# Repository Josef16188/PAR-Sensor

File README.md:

FloraFlux – PAR Sensor

FloraFlux is a custom-built sensor for measuring Photosynthetic Photon Flux Density (PPFD) and calculating the Daily Light Integral (DLI) for plant-light monitoring.

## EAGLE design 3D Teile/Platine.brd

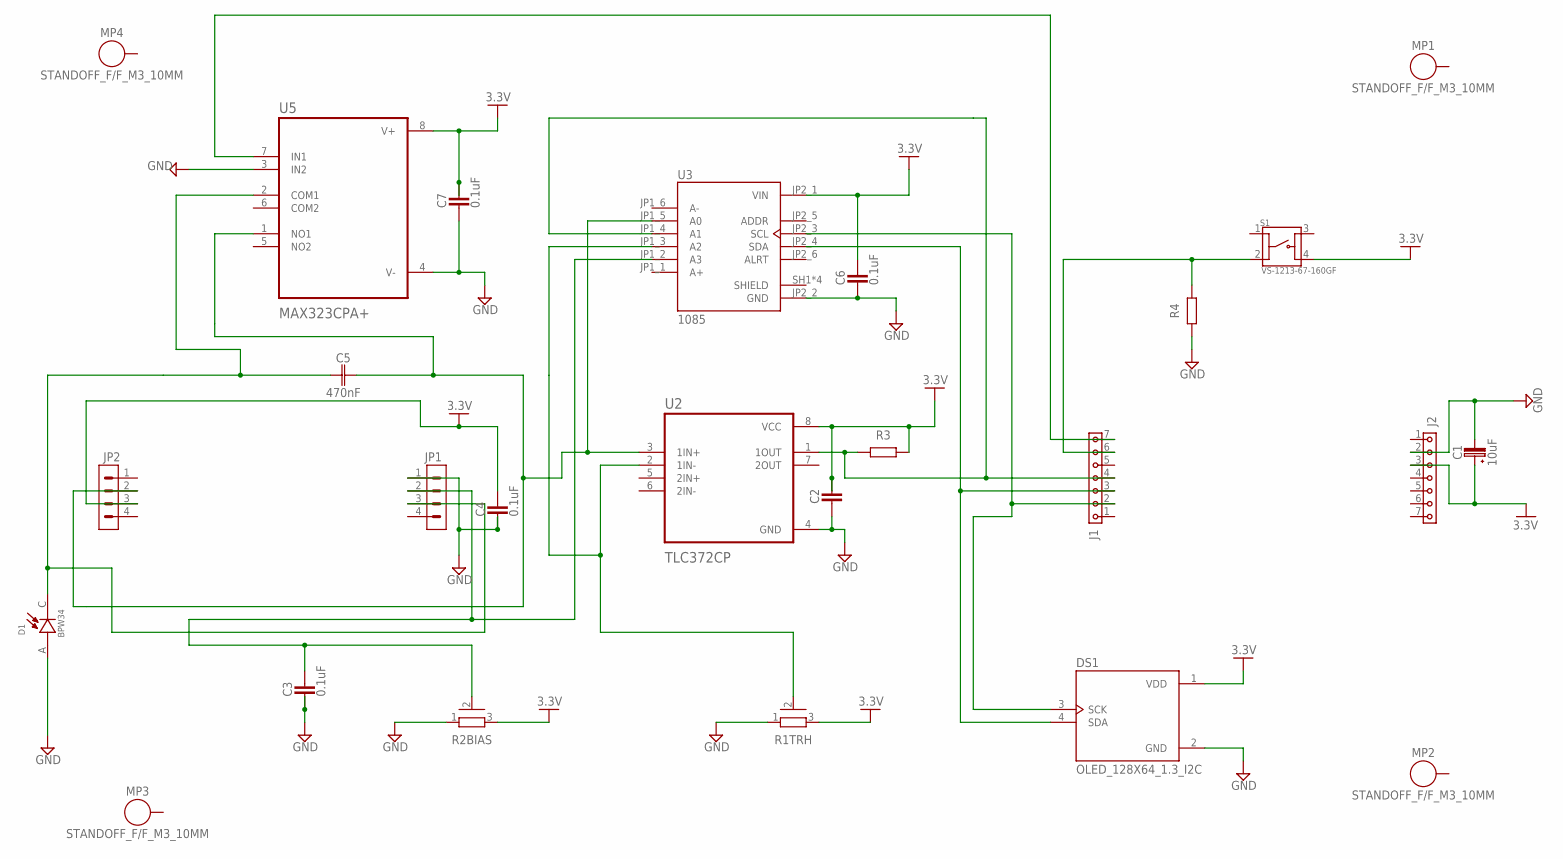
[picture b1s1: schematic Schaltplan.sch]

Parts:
C1: 10uF; CAPPRD508W65D1000H1100B
C2: CAPACITORCERAMIC-2.54MM; CAP-THRU-2.54MM
C3, C4, C6, C7: 0.1uF; CAP-THRU-2.54MM
C5: 470nF; CAPRD550W60D1025H1250B
D1: BPW34; DIO_BPW34
DS1: OLED_128X64_1.3_I2C; LCD_OLED_128X64_1.3_I2C
J1, J2: 6130XX11821_61300711821; 61300711821
JP1, JP2: PINHD-1X4; 1X04
MP1, MP2, MP3, MP4: STANDOFF_F/F_M3_10MM; STANDOFF_HEX_FEMALE_550X1000_M3X0.5_MTGP850H320
R1TRH, R2BIAS: PV36Y
R3, R4: R_AXIAL-11.7MM-PITCH; RESAD1176W63L850D250B
S1: VS-1213-67-160GF; SW_VS-1213-67-160GF
U2: TLC372CP; DIP794W45P254L959H508Q8
U3: 1085; MODULE_1085
U5: MAX323CPA+; DIP794W47P254L991H457Q8

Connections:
3.3V: C1.1 (+), C2.1, C4.1, C6.1, C7.1, DS1.1 (VDD), J2.3, JP2.3, R1TRH.3, R2BIAS.3, R3.2, S1.4, U2.8 (VCC), U3.JP2_1 (VIN), U5.8 (V+)
GND: C1.2 (-), C2.2, C3.2, C4.2, C6.2, C7.2, D1.A, DS1.2 (GND), J2.2, JP1.1, R1TRH.1, R2BIAS.1, R4.1, U2.4 (GND), U3.JP2_2 (GND), U5.3 (IN2), U5.4 (V-)
unnamed: C3.1, JP1.2, R2BIAS.2, U3.JP1_2 (A3)
unnamed: R1TRH.2, U2.2 (1IN-), U3.JP1_3 (A2)
unnamed: J1.7, U5.7 (IN1)
unnamed: J1.6, R4.2, S1.2
unnamed: J1.4, R3.1, U2.1 (1OUT), U3.JP1_4 (A1)
unnamed: DS1.4 (SDA), J1.3, U3.JP2_4 (SDA)
unnamed: DS1.3 (SCK), J1.2, U3.JP2_3 (SCL)
unnamed: C5.2, JP2.2, U2.3 (1IN+), U3.JP1_5 (A0), U5.1 (NO1)
unnamed: C5.1, D1.C, JP1.3, U5.2 (COM1)

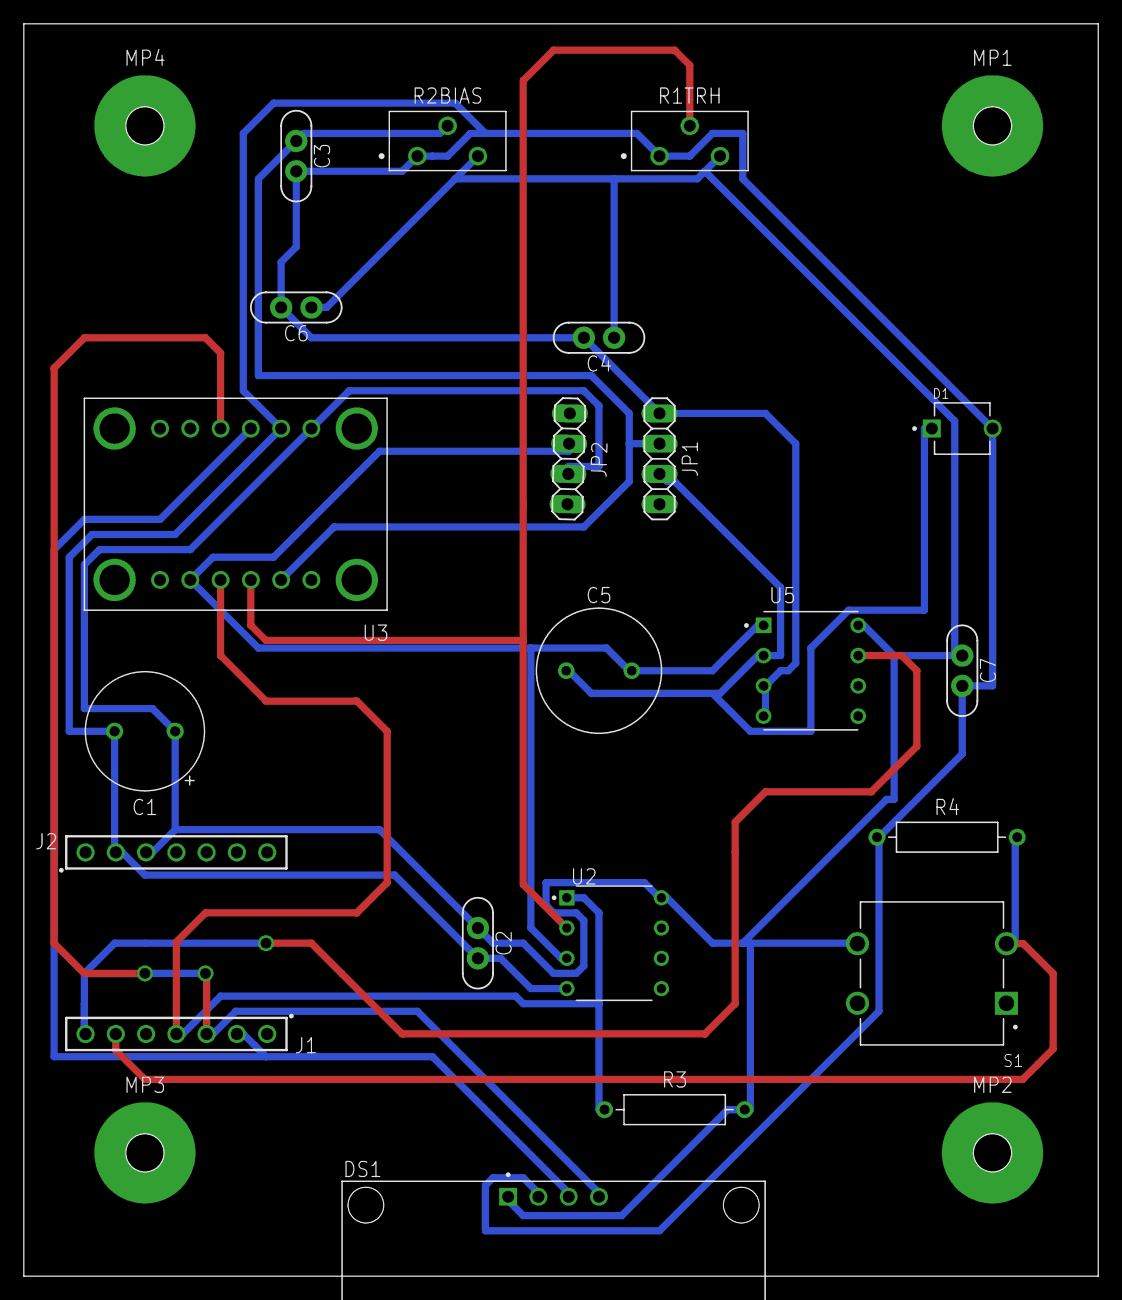
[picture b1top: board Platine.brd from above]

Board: 2 copper layers, 90.2 x 105.1 mm, 25 parts (0 on the bottom side), 11 nets.
